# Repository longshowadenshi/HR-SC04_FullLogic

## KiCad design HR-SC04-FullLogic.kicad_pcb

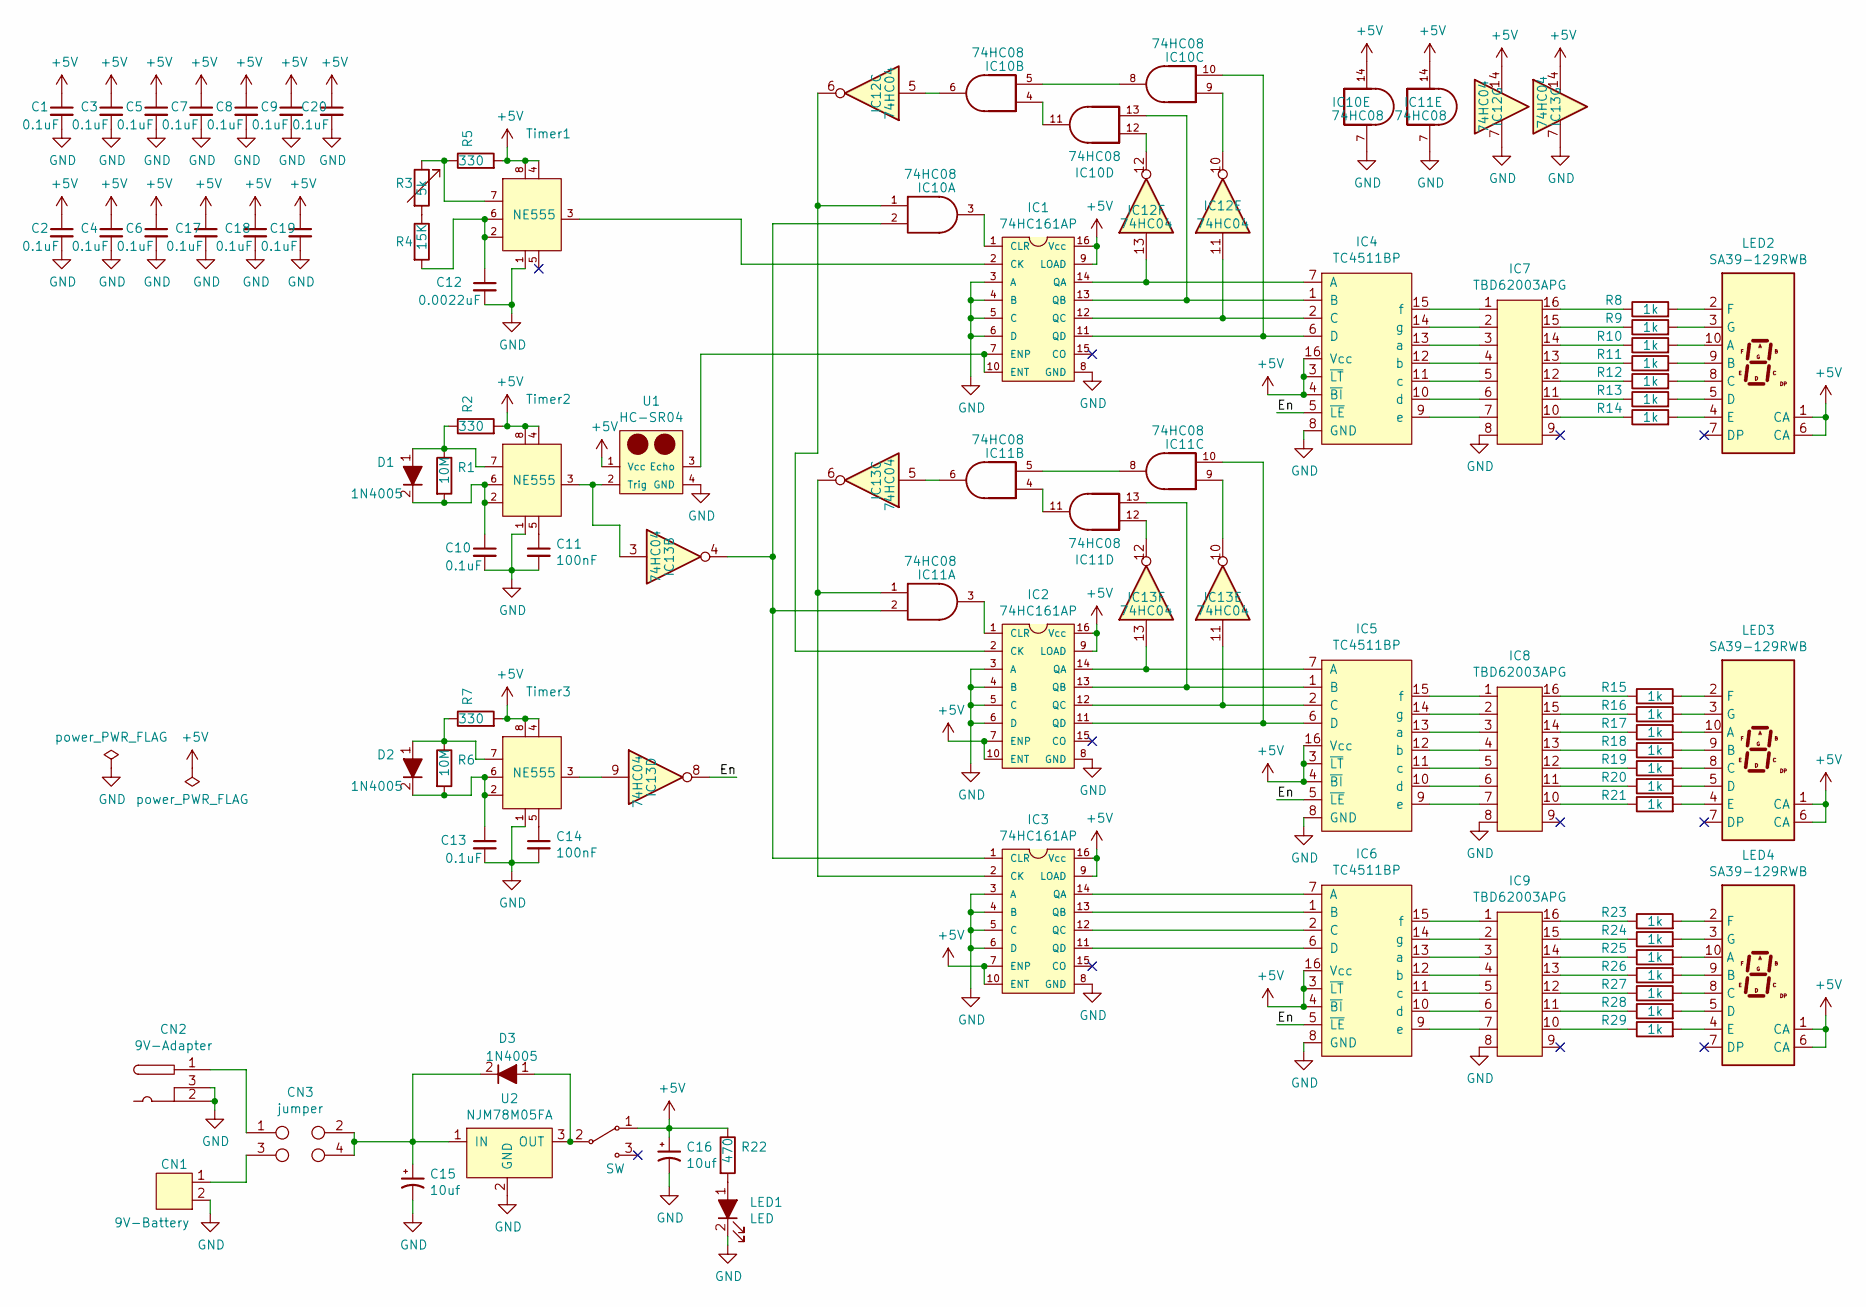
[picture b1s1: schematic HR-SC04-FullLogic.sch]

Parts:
C1, C2, C3, C4, C5, C6, C7, C8, C9, C17, C18, C19, C20: 0.1uF; C0603C104Z3VACTU
C10, C13: 0.1uF; 0.1uf-bypass
C11, C14: 100nF; C-2.54
C12: 0.0022uF; C-2.54
C15, C16: 10uf; 10uF-16v
CN1: 9V-Battery; XH-2pins
CN2: 9V-Adapter; MJ179P
CN3: jumper
D1, D2, D3: 1N4005; 1DS4
IC1, IC2, IC3: 74HC161AP
IC4, IC5, IC6: TC4511BP; 74HC161AP
IC7, IC8, IC9: TBD62003APG; 74HC161AP
IC10, IC11: 74HC08; 74HC04
IC12, IC13: 74HC04
LED1: LED; C1608C0G1H682J
LED2, LED3, LED4: SA39-129RWB
R1, R6: 10M; R
R2, R5, R7: 330; R
R3: 5k; CT-6P
R4: 15K; R
R8, R9, R10, R11, R12, R13, R14, R15, R16, R17, R18, R19, R20, R21, R23, R24, R25, R26, R27, R28, R29: 1k; C_1220
R22: 470; C1608C0G1H682J
SW1: SW; SS-12D01G3
Timer1, Timer2, Timer3: NE555; DIP794W45P254L1060H508Q8
U1: HC-SR04; HCSR04
U2: NJM78M05FA

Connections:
+5V: C1.1, C2.1, C3.1, C4.1, C5.1, C6.1, C7.1, C8.1, C9.1, C16.1, C17.1, C18.1, C19.1, C20.1, IC1.9 (LOAD), IC1.16 (Vcc), IC2.7 (ENP), IC2.9 (LOAD), IC2.10 (ENT), IC2.16 (Vcc), IC3.7 (ENP), IC3.9 (LOAD), IC3.10 (ENT), IC3.16 (Vcc), IC4.3 (~LT), IC4.4 (~BI), IC4.16 (Vcc), IC5.3 (~LT), IC5.4 (~BI), IC5.16 (Vcc), IC6.3 (~LT), IC6.4 (~BI), IC6.16 (Vcc), IC10.14, IC11.14, IC12.14, IC13.14, LED2.1 (CA), LED2.6 (CA), LED3.1 (CA), LED3.6 (CA), LED4.1 (CA), LED4.6 (CA), R2.2, R5.2, R7.2, R22.1, SW1.1, Timer1.4, Timer1.8, Timer2.4, Timer2.8, Timer3.4, Timer3.8, U1.1 (Vcc)
/En: IC4.5 (~LE), IC5.5 (~LE), IC6.5 (~LE), IC13.8
GND: C1.2, C2.2, C3.2, C4.2, C5.2, C6.2, C7.2, C8.2, C9.2, C10.2, C11.2, C12.2, C13.2, C14.2, C15.2, C16.2, C17.2, C18.2, C19.2, C20.2, CN1.2, CN2.2, CN2.3, IC1.3 (A), IC1.4 (B), IC1.5 (C), IC1.6 (D), IC1.8 (GND), IC2.3 (A), IC2.4 (B), IC2.5 (C), IC2.6 (D), IC2.8 (GND), IC3.3 (A), IC3.4 (B), IC3.5 (C), IC3.6 (D), IC3.8 (GND), IC4.8 (GND), IC5.8 (GND), IC6.8 (GND), IC7.8, IC8.8, IC9.8, IC10.7, IC11.7, IC12.7, IC13.7, LED1.2, Timer1.1, Timer2.1, Timer3.1, U1.4 (GND), U2.2 (GND)
unnamed: C10.1, D1.2, R1.2, Timer2.2, Timer2.6
unnamed: C11.1, Timer2.5
unnamed: C12.1, R4.2, Timer1.2, Timer1.6
unnamed: C13.1, D2.2, R6.2, Timer3.2, Timer3.6
unnamed: C14.1, Timer3.5
unnamed: C15.1, CN3.2, CN3.4, D3.2, U2.1 (IN)
unnamed: CN1.1, CN3.3
unnamed: CN2.1, CN3.1
unnamed: D1.1, R1.1, R2.1, Timer2.7
unnamed: D2.1, R6.1, R7.1, Timer3.7
unnamed: D3.1, SW1.2, U2.3 (OUT)
unnamed: IC1.1 (CLR), IC10.3
unnamed: IC1.2 (CK), Timer1.3
unnamed: IC1.7 (ENP), IC1.10 (ENT), U1.3 (Echo)
unnamed: IC1.11 (QD), IC4.6 (D), IC10.10
unnamed: IC1.12 (QC), IC4.2 (C), IC12.11
unnamed: IC1.13 (QB), IC4.1 (B), IC10.13
unnamed: IC1.14 (QA), IC4.7 (A), IC12.13
unnamed: IC3.11 (QD), IC6.6 (D)
unnamed: IC3.12 (QC), IC6.2 (C)
unnamed: IC3.13 (QB), IC6.1 (B)
unnamed: IC3.14 (QA), IC6.7 (A)
unnamed: IC4.9 (e), IC7.7
unnamed: IC4.10 (d), IC7.6
unnamed: IC4.11 (c), IC7.5
unnamed: IC4.12 (b), IC7.4
unnamed: IC4.13 (a), IC7.3
unnamed: IC4.14 (g), IC7.2
unnamed: IC4.15 (f), IC7.1
unnamed: IC5.9 (e), IC8.7
unnamed: IC5.10 (d), IC8.6
unnamed: IC5.11 (c), IC8.5
unnamed: IC5.12 (b), IC8.4
unnamed: IC5.13 (a), IC8.3
unnamed: IC5.14 (g), IC8.2
unnamed: IC5.15 (f), IC8.1
unnamed: IC6.9 (e), IC9.7
unnamed: IC6.10 (d), IC9.6
unnamed: IC6.11 (c), IC9.5
unnamed: IC6.12 (b), IC9.4
unnamed: IC6.13 (a), IC9.3
unnamed: IC6.14 (g), IC9.2
unnamed: IC6.15 (f), IC9.1
unnamed: IC7.10, R14.1
unnamed: IC7.11, R13.1
unnamed: IC7.12, R12.1
unnamed: IC7.13, R11.1
unnamed: IC7.14, R10.1
unnamed: IC7.15, R9.1
unnamed: IC7.16, R8.1
unnamed: IC8.10, R21.1
unnamed: IC8.11, R20.1
unnamed: IC8.12, R19.1
unnamed: IC8.13, R18.1
unnamed: IC8.14, R17.1
unnamed: IC8.15, R16.1
unnamed: IC8.16, R15.1
unnamed: IC9.10, R29.1
unnamed: IC9.11, R28.1
unnamed: IC9.12, R27.1
unnamed: IC9.13, R26.1
unnamed: IC9.14, R25.1
unnamed: IC9.15, R24.1
unnamed: IC9.16, R23.1
unnamed: IC2.2 (CK), IC10.1, IC12.6
unnamed: IC3.1 (CLR), IC10.2, IC11.2, IC13.4
unnamed: IC10.5, IC10.8
unnamed: IC10.6, IC12.5
unnamed: IC10.9, IC12.10
unnamed: IC10.4, IC10.11
unnamed: IC10.12, IC12.12
unnamed: IC3.2 (CK), IC11.1, IC13.6
unnamed: IC2.1 (CLR), IC11.3
unnamed: IC11.5, IC11.8
unnamed: IC11.6, IC13.5
unnamed: IC11.9, IC13.10
unnamed: IC2.11 (QD), IC5.6 (D), IC11.10
unnamed: IC11.4, IC11.11
unnamed: IC11.12, IC13.12
unnamed: IC2.13 (QB), IC5.1 (B), IC11.13
unnamed: IC13.3, Timer2.3, U1.2 (Trig)
unnamed: IC13.9, Timer3.3
unnamed: IC2.12 (QC), IC5.2 (C), IC13.11
unnamed: IC2.14 (QA), IC5.7 (A), IC13.13
unnamed: LED1.1, R22.2
unnamed: LED2.2 (F), R8.2
unnamed: LED2.3 (G), R9.2
unnamed: LED2.4 (E), R14.2
unnamed: LED2.5 (D), R13.2
unnamed: LED2.8 (C), R12.2
unnamed: LED2.9 (B), R11.2
unnamed: LED2.10 (A), R10.2
unnamed: LED3.2 (F), R15.2
unnamed: LED3.3 (G), R16.2
unnamed: LED3.4 (E), R21.2
unnamed: LED3.5 (D), R20.2
unnamed: LED3.8 (C), R19.2
unnamed: LED3.9 (B), R18.2
unnamed: LED3.10 (A), R17.2
unnamed: LED4.2 (F), R23.2
unnamed: LED4.3 (G), R24.2
unnamed: LED4.4 (E), R29.2
unnamed: LED4.5 (D), R28.2
unnamed: LED4.8 (C), R27.2
unnamed: LED4.9 (B), R26.2
unnamed: LED4.10 (A), R25.2
unnamed: R3.1, R5.1, Timer1.7
unnamed: R3.2, R4.1

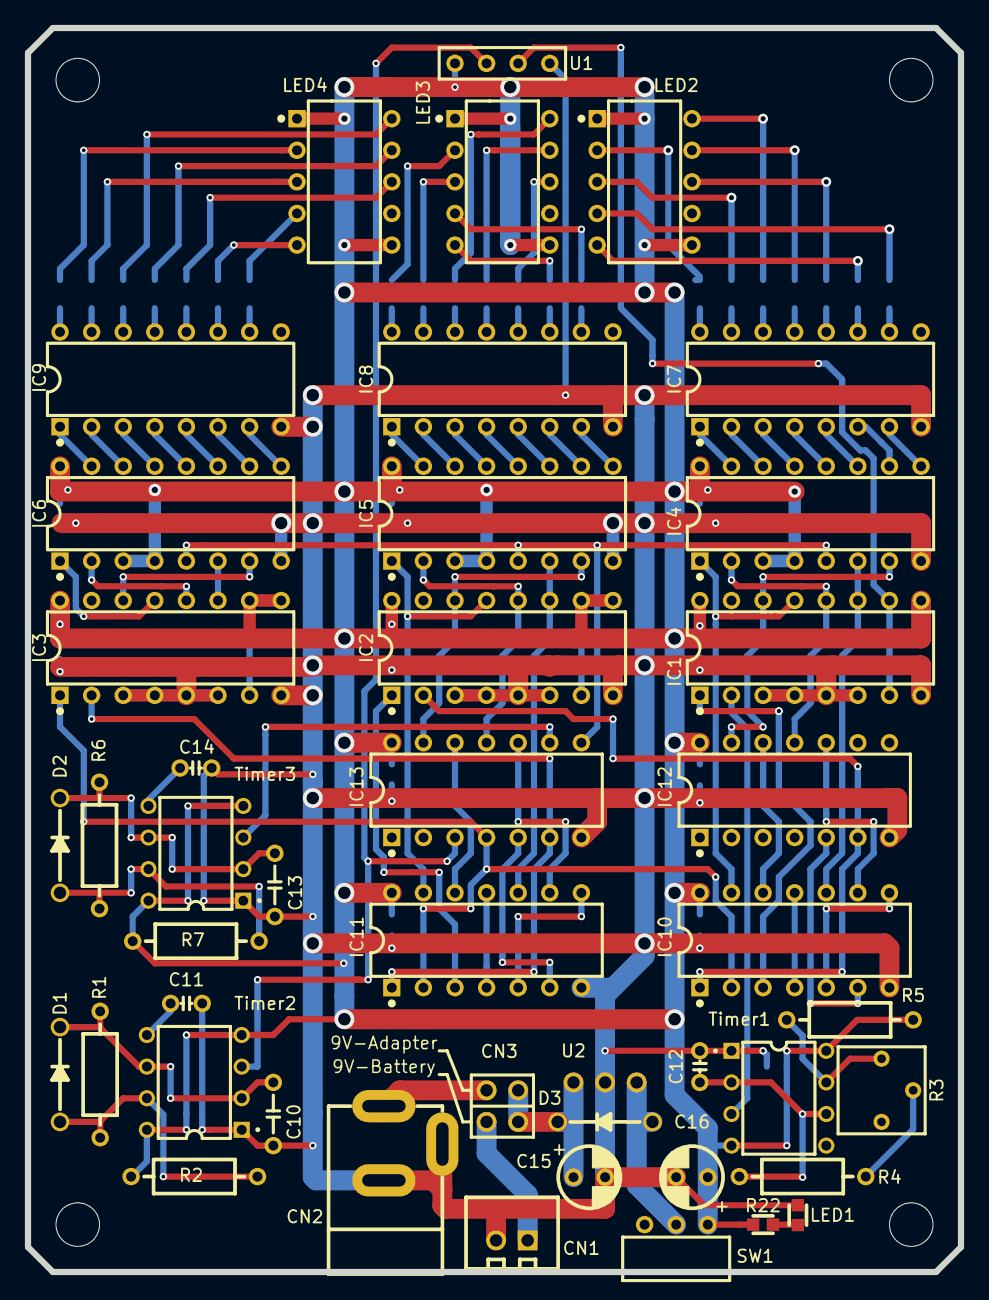
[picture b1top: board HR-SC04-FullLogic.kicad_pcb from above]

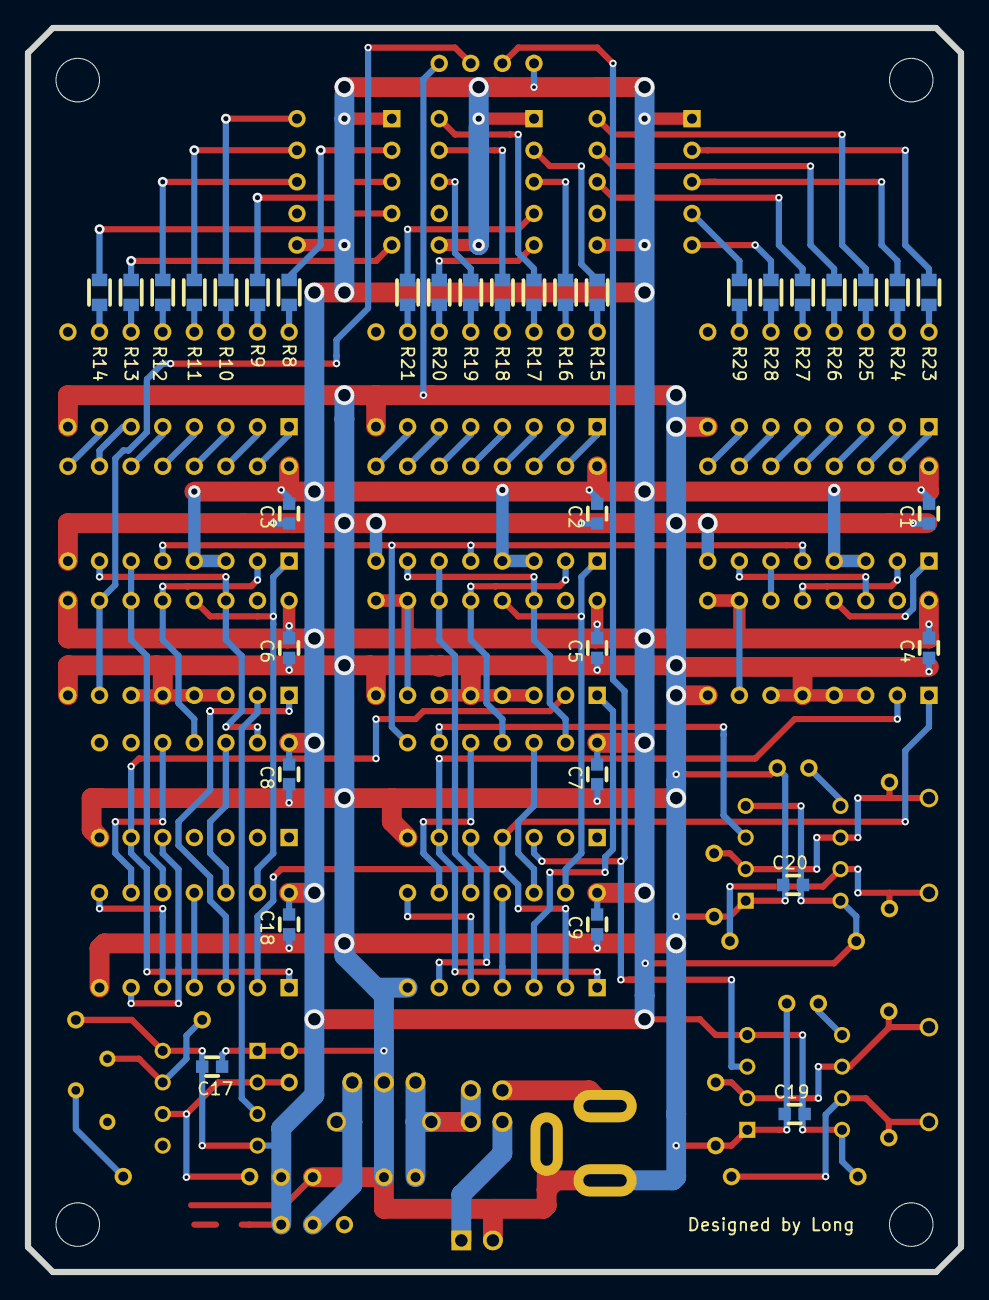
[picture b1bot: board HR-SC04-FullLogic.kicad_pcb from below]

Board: 2 copper layers, 75.0 x 100.0 mm, 78 parts (34 on the bottom side), 111 nets.
